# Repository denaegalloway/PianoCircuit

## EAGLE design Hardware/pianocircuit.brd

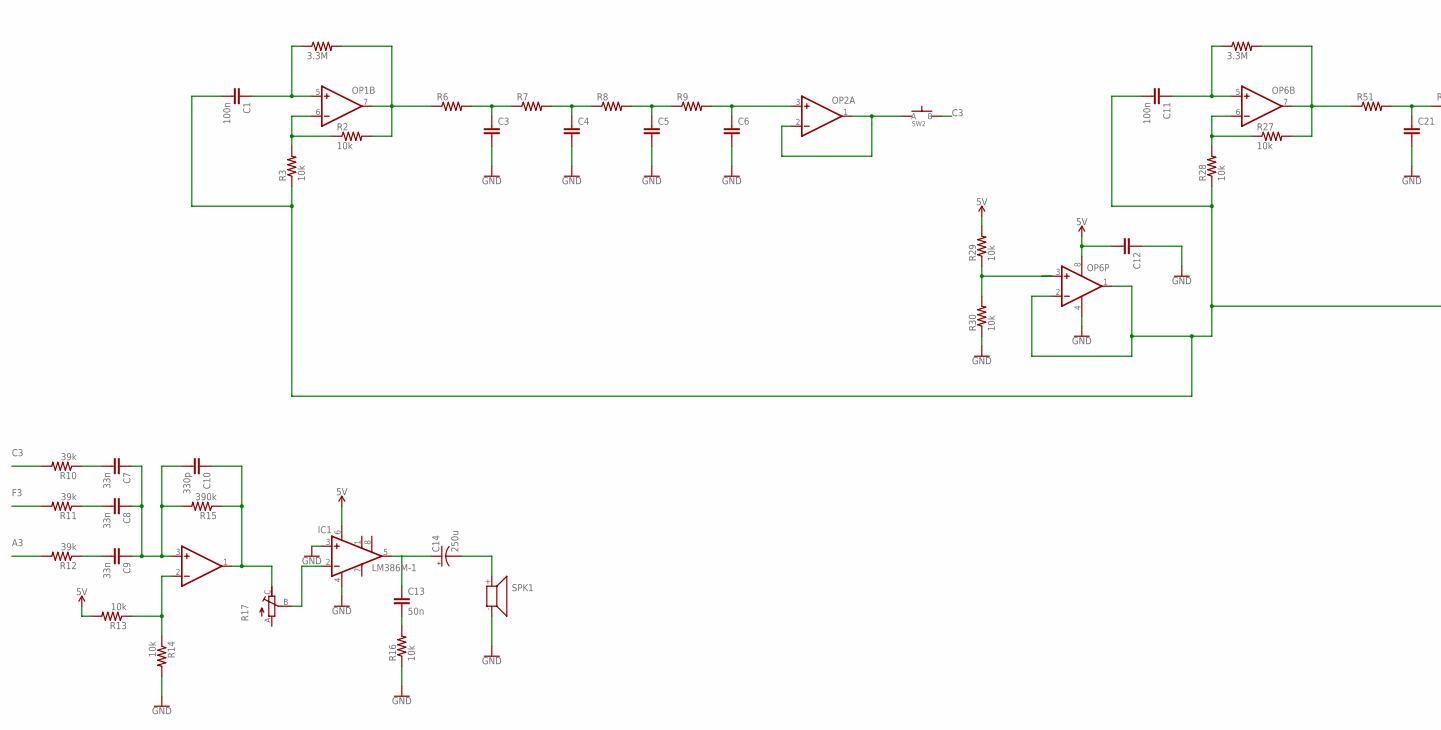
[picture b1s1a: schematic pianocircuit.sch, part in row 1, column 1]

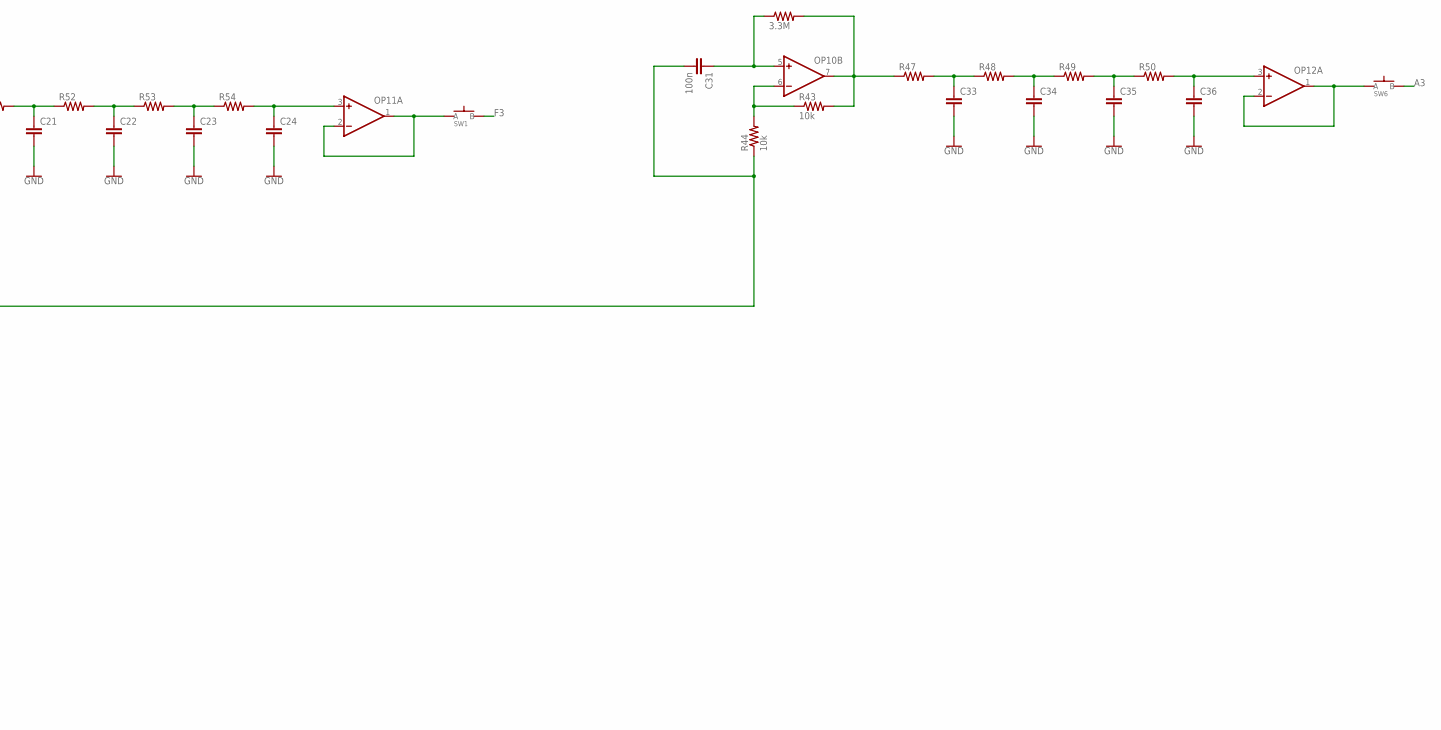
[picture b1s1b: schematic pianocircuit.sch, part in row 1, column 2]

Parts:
C1, C11, C31: 100n; C0603
C3, C4, C5, C6, C12, C21, C22, C23, C24, C33, C34, C35, C36: CAPACITOR0603; C0603
C7, C8, C9: 33n; C0603
C10: 330p; C0603
C13: 50n; C0603
C14: 250u; C-EEU-FM-A-220UF
IC1: LM386M-1; SO08
OP1, OP2, OP3, OP6, OP10, OP11, OP12: OP-DUALR; SO8
R1, R4, R26: 3.3M; R0603
R2, R3, R13, R14, R16, R27, R28, R29, R30, R43, R44: 10k; R0603
R6, R7, R8, R9, R47, R48, R49, R50, R51, R52, R53, R54: RESISTOR0603; R0603
R10, R11, R12: 39k; R0603
R15: 390k; R0603
R17: R-TRIMM-CB10V; RTRIMCB10
SPK1: SPEAKER; SOLDER.TABS
SW1, SW2, SW6: SPST.KT11P4SM34LFS

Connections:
A3: R12.2, SW6.3 (B), SW6.4 (B)
C3: R10.2, SW2.3 (B), SW2.4 (B)
F3: R11.2, SW1.3 (B), SW1.4 (B)
unnamed: C1.2, C11.2, C31.2, OP6.1 (OUT), OP6.2 (-IN), R3.1, R28.1, R44.1
unnamed: OP1.6 (-IN), R2.1, R3.2
unnamed: C1.1, OP1.5 (+IN), R1.1
unnamed: OP1.7 (OUT), R1.2, R2.2, R6.1
unnamed: C3.1, R6.2, R7.1
unnamed: C4.1, R7.2, R8.1
unnamed: C5.1, R8.2, R9.1
unnamed: C6.1, OP2.3 (+IN), R9.2
unnamed: OP2.1 (OUT), OP2.2 (-IN), SW2.1 (A), SW2.2 (A)
unnamed: C7.2, R10.1
unnamed: C7.1, C8.1, C9.1, C10.2, OP3.3 (+IN), R15.2
unnamed: C9.2, R12.1
unnamed: C8.2, R11.1
unnamed: C10.1, OP3.1 (OUT), R15.1, R17.C (E)
unnamed: OP3.2 (-IN), R13.1, R14.1
unnamed: IC1.2 (-IN), R17.B (S)
unnamed: C13.2, R16.2
unnamed: C13.1, C14.+, IC1.5 (OUT)
unnamed: OP6.3 (+IN), R29.1, R30.2
unnamed: OP6.6 (-IN), R27.1, R28.2
unnamed: C11.1, OP6.5 (+IN), R26.1
unnamed: OP6.7 (OUT), R26.2, R27.2, R51.1
unnamed: C14.-, SPK1.+
unnamed: C21.1, R51.2, R52.1
unnamed: C22.1, R52.2, R53.1
unnamed: C23.1, R53.2, R54.1
unnamed: C24.1, OP11.3 (+IN), R54.2
unnamed: OP11.1 (OUT), OP11.2 (-IN), SW1.1 (A), SW1.2 (A)
unnamed: OP10.6 (-IN), R43.1, R44.2
unnamed: C31.1, OP10.5 (+IN), R4.1
unnamed: OP10.7 (OUT), R43.2, R47.1
unnamed: C33.1, R47.2, R48.1
unnamed: C34.1, R48.2, R49.1
unnamed: C35.1, R49.2, R50.1
unnamed: C36.1, OP12.3 (+IN), R50.2
unnamed: OP12.1 (OUT), OP12.2 (-IN), SW6.1 (A), SW6.2 (A)
V+: C12.2, IC1.6 (VS), OP1.8 (V+), OP2.8 (V+), OP3.8 (V+), OP6.8 (V+), OP10.8 (V+), OP11.8 (V+), OP12.8 (V+), R13.2, R29.2
V-: C3.2, C4.2, C5.2, C6.2, C21.2, C22.2, C23.2, C24.2, C33.2, C34.2, C35.2, C36.2, IC1.3 (+IN), IC1.4 (GND), OP1.4 (V-), OP2.4 (V-), OP3.4 (V-), OP6.4 (V-), OP10.4 (V-), OP11.4 (V-), OP12.4 (V-), R14.2, R16.1, R30.1, SPK1.-

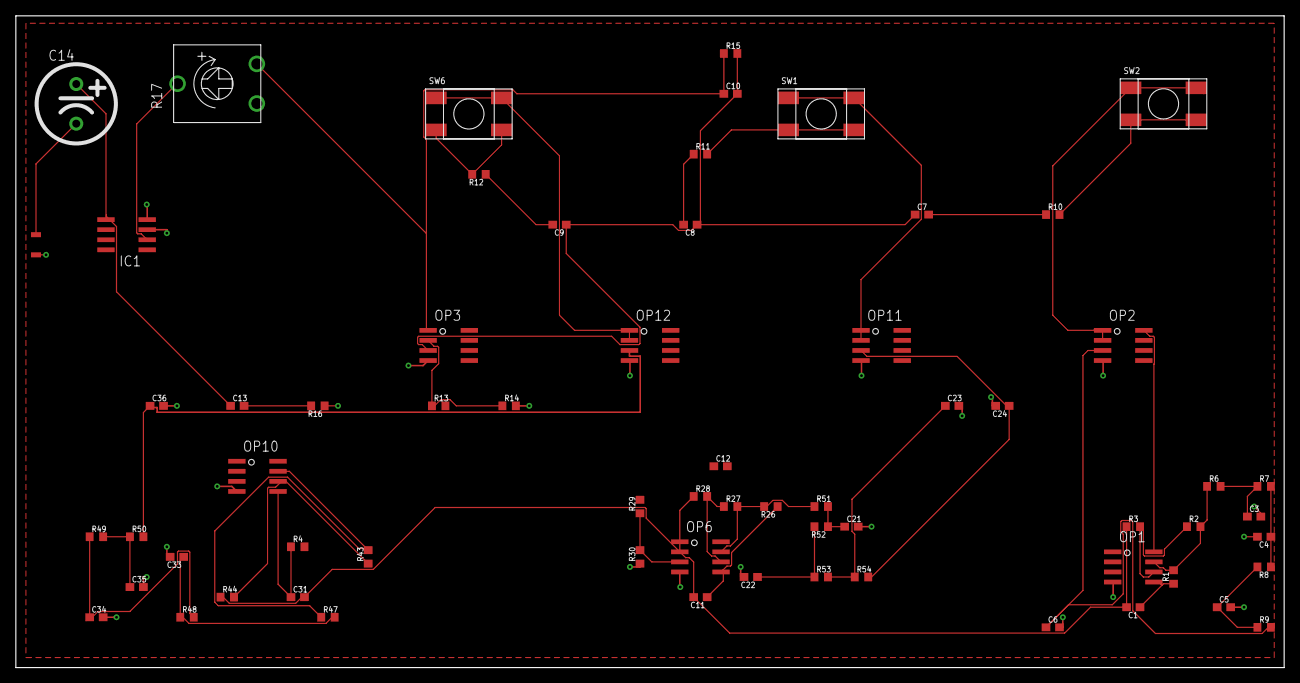
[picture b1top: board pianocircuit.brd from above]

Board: 2 copper layers, 160.0 x 82.2 mm, 65 parts (0 on the bottom side), 41 nets.

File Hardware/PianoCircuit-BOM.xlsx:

Design Name -- Revision Code / Designer or Organization Name |  |  |  |  |  |  |  |  |  |  | Total | 36.25 | Total (in Bulk) | 582.74710000000005
BOM # | Comment | Designator | Description | Mounting Type | Package | Manufacturer | Manufacturer Part Number | Supplier | Supplier Part Number | Price per unit | Quantity | Total | Per 100 | Total
1 | LM358 | OP1 | General Purpose Amplifier 2 Circuit 8-SOIC | SMD | 8-SOIC | Texas Instruments | LM358DR | Digi-Key | 296-1014-1-ND | 0.38 | 1 | 0.38 | 0.1391 | 0.1391
2 | Photoresistor | Photo | CDS Cell 520nm 27 ~ 60kOhms @ 10 lux | THT | Radial | Advanced Photonix | PDV-P8104 | Digi-Key | PDV-P8104-ND | 0.89 | 1 | 0.89 | 0.46 | 0.46
3 | 9V Battery Connector | 9V | Battery Connector, Snap 9V 1 Cell Wire Leads - 4" (101.6mm) | THT |  | Keystone Electronics | 81-4 | Digi-Key | 36-81-4-ND | 0.55000000000000004 | 1 | 0.55000000000000004 | 0.3982 | 0.3982
4 | White LED | LED1 | White LED Indication - Discrete 2.9V Radial | THT | Radial | American Bright Optoelectronics Corporation | BL-BZX3V4V-1-B02 | Digi-Key | BL-BZX3V4V-1-B02-ND | 0.26 | 1 | 0.26 | 9.0899999999999995E-2 | 9.0899999999999995E-2
5 | 10k resistor | R1,R2,R3 | 10 kOhms ±1% 0.1W, 1/10W Chip Resistor 0603 (1608 Metric) Automotive AEC-Q200 T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 | SMD | 0603 | Stackpole Electronics Inc | RMCF0603FT10K0 | Digi-Key | RMCF0603FT10K0CT-ND | 0.1 | 3 | 0.30000000000000004 | 6.7999999999999996E-3 | 2.0399999999999998E-2
6 | 1uF capacitor | C1 | 1µF ±10% 25V Ceramic Capacitor X5R 0603 (1608 Metric) | SMD | 0603 | Samsung Electro-Mechanics | CL10A105KA8NNNC | Digi-Key | 1276-1102-1-ND | 0.1 | 1 | 0.1 | 1.8499999999999999E-2 | 1.8499999999999999E-2
1 | 10k resistor | R2, R3, R13, R14, R16, R29, R30, R28, R27, R44, R43 | 10 kOhms ±1%, 1/4W Through Hole Resistor Axial Flame Retardant Coating, Safety 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 | THT |  | Stackpole Electronics Inc | RNF14FTD10K0 | Digi-Key | RNF14FTD10K0CT-ND | 0.1 | 11 | 1.1000000000000001 | 2.5 | 2.5
2 | 3.3M resistor | R1, R4, R26 | 3.3M Ohms ±5%, 1/8W Through Hole Resistor Axial Flame Retardant Coating, Safety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 | THT |  | Stackpole Electronics Inc | CF18JT3M30 | Digi-Key | CF18JT3M30CT-ND | 0.1 | 3 | 0.3 | 1.83 | 1.83
3 | 5V Battery | 5V
4 | 100 nF capacitor | C1, C11, C31 | Ceramic Capacitor , Y5V, 0805, 0.1UF, +80/-20% | SMD | 0805 | Stackpole Electronics Inc | CML0805Y5V104ZT50V | Digi-Key | 738-CML0805Y5V104ZT50VCT-ND | 0.1 | 3 | 0.3 | 3.38 | 3.38
5 | 10 nF capacitor | C3, C4, C5, C6, C21, C22, C23, C24, C33 C34, C35, C36 | 10000 pF ± 10% 16V Ceramic Capacitor X7R 0402 (1005 Metric) | SMD | 0402 | Samsung Electro-Mechanics | CL05B103KO5NNNC | Digi-Key | 1276-1051-1-ND | 0.1 | 10 | 1 | 0.74 | 0.74
6 | 33 nF capacitor | C7, C8, C9 | 33 nF ±20% 50V Ceramic Capacitor Z5U Radial | THT | Radial | NTE Electronics Inc | CML333M50 | Digi-Key | 2368-CML333M50-ND | 0.16200000000000001 | 3 | 0.48 | 14.94 | 14.94
7 | 39k resistor | R10, R11, R12 | 39 kOhms ± 5%, 1/10W Chip Resistor 0603 (1608 Metric) Automotive AEC-Q200 Thick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 | SMD | 0603 | Panasonic Electronic Components | ERJ-3GEYJ393V | Digi-Key | P39KGCT-ND | 0.1 | 3 | 0.3 | 1.36 | 1.36
8 | 330pF capacitor | C10 | 330PF 50V X7R 0603 | SMD | 0603 | Stackpole Electronics Inc | CML0603X7R331KT50V | Digi-Key | 738-CML0603X7R331KT50VCT-ND | 0.1 | 1 | 0.1 | 2.25 | 2.25
9 | 390k resistor | R15 | 390 kOhms ± 5%, 1/10W Chip Resistor 0603(1608 Metric) Automotive AEC-Q200 Thick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 | SMD | 0603 | Stackpole Electronics Inc | RMCF0603JT390K | Digi-Key | RMCF0604JT390KCT-ND | 0.1 | 1 | 0.1 | 0.61 | 0.61
10 | LM386M-1 | IC1 | Amplifier IC 1-channel (Mono) Class AB 8-SOIC |  | 8-SOIC | Rochester Electronics, LLC | LM386M-1 | Digi-Key | 2156-LM386M-1-ND | 0.48 | 1 | 0.48
11 | R-TRIMM-CB10V | R17
12 | 50 nF capacitor | C13 | 47 nF ±10% 50V Ceramic Capacitor BX Radial | THT | Radial | KEMET | CK05BX473K | Digi-Key | 1001-2023-ND | 1.05 | 1 | 1.05 | 62.39 | 62.39
13 | 250 uF capacitor | C14
14 | Speaker | SPK1
15 | OP-DUALR | OP1, OP2, OP6, OP10, OP11, OP12 | CMOS Amplifier Circuit Rail-to-Rail 8-MSOP | SMD | 8-MSOP | Analog Devices Inc | AD8607ARMZ | Digi-Key | AD8607ARMZ-ND | 2.95 | 6 | 17.7 | 217.04 | 217.04
16 | Switch | SW1, SW2, SW3 | Tactile Switch SPST-NO Top Actuated Surface Mount | SMD |  | C&K | KT11P4SM34LFS | Digi-Key | CKN1860CT-ND | 3.62 | 3 | 10.86 | 274.58 | 274.58

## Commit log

2021-02-27 Pianocircuit
2021-02-27 Remove Redundant Folder
2021-02-27 brd & BOM
2021-02-27 Added correct file
2021-03-06 updated schematic
2021-03-13 Full Schematic
2021-03-13 Began Board Layout
2021-03-13 Board Routing
2021-03-20 Updated Board Routing
2021-03-20 Reorganizing Board
2021-03-20 Reorganized
2021-03-27 Updated Routing
2021-03-27 Routed Board and Updated Schematic
2021-03-29 Updated BOM (not complete)
2021-04-03 Fixed Routing Errors
2021-04-03 Updated BOM
2021-04-17 board and schematic
2021-04-17 Fixed inconsistent board and schematic
